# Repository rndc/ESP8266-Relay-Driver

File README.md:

# ESP8266 (ESP-01) Relay Driver Breakout Board
Simple 5V relay driver breakout board for ESP-01. Left pinout from top to bottom:

1. Vcc (5V)
2. GND
3. Relay

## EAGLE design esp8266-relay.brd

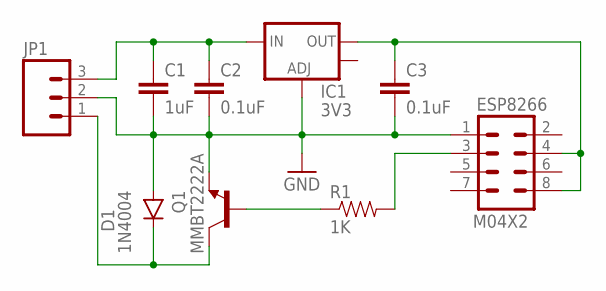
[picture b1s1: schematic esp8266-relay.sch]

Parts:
C1: 1uF; 0603-CAP
C2, C3: 0.1uF; 0805
D1: 1N4004; SMA-DIODE_ALT
ESP8266: M04X2; 2X4
IC1: 3V3; SOT223
JP1: M03PTH; 1X03
Q1: MMBT2222A; SOT23-3
R1: 1K; 0603-RES

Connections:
GND: C1.2, C2.2, C3.2, D1.A, ESP8266.1, IC1.1 (ADJ), JP1.2, Q1.2 (E)
unnamed: C1.1, C2.1, IC1.3 (IN), JP1.3
unnamed: C3.1, ESP8266.4, ESP8266.8, IC1.2 (OUT)
unnamed: D1.C, JP1.1, Q1.3 (C)
unnamed: Q1.1 (B), R1.1
unnamed: ESP8266.3, R1.2

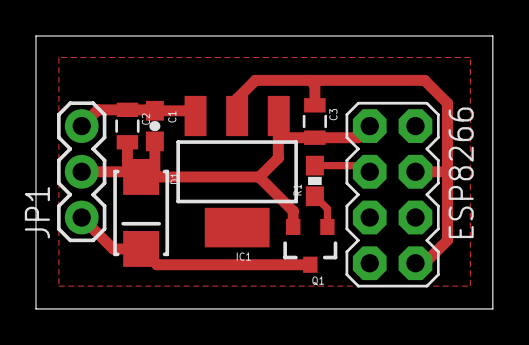
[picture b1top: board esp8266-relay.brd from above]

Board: 2 copper layers, 25.4 x 15.2 mm, 9 parts (0 on the bottom side), 6 nets.

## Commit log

2015-05-06 :sparkles: Initial commit

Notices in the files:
parts and their libraries:
SparkFun-Passives: Licensing: Creative Commons ShareAlike 4.0 International - https://creativecommons.org/licenses/by-sa/4.0
